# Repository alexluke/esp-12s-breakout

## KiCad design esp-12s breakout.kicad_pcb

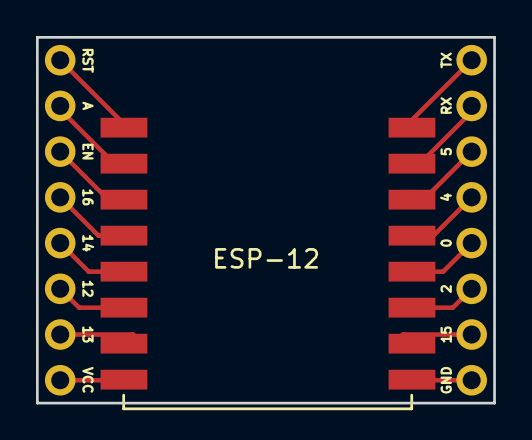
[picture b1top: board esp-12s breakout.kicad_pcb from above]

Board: 2 copper layers, 25.4 x 20.3 mm, 3 parts (0 on the bottom side), 16 nets.

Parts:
ESP-12: ESP-12
P1, P2: CONN_01X08; Pin_Header_Straight_1x08_Pitch2.54mm

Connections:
/GND: ESP-12.9, P2.8
/VCC: ESP-12.8, P1.8
unnamed: ESP-12.1, P1.1
unnamed: ESP-12.2, P1.2
unnamed: ESP-12.3, P1.3
unnamed: ESP-12.4, P1.4
unnamed: ESP-12.5, P1.5
unnamed: ESP-12.6, P1.6
unnamed: ESP-12.7, P1.7
unnamed: ESP-12.16, P2.1
unnamed: ESP-12.15, P2.2
unnamed: ESP-12.14, P2.3
unnamed: ESP-12.13, P2.4
unnamed: ESP-12.12, P2.5
unnamed: ESP-12.11, P2.6
unnamed: ESP-12.10, P2.7

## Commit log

2017-05-29 ESP-12S breakout
